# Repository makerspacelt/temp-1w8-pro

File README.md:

---

## ⚠️ __NEW USERS__
To set up your device with latest ESPHome config go to https://temp-1w8-pro.makerspace.lt/update

Latest ESPHome `*.yaml` file could be found in a dedicated software repository of this device: https://github.com/makerspacelt/temp-1w8-pro-sw

## About
This device is meant for temperature monitoring with up to 8 thermometers.

Basic target features:

* 8x 1-wire interfaces for DS18b20 using 2.5mm 4p audio jack connectors
* 2x user programmable buttons (can be used to wake up from deep sleep)
* 128x64 OLED display
* Powered via USB-C
* Compatibility with esphome and Home Assistant

Dev NOTE: before commit, run `./kibot.sh` to regenerate documentation, bom, gerbers and other assets.

* [schematics.pdf](gen/schematics.pdf)
* [pcb.pdf with dimensions](gen/pcb.pdf)
* [ibom.html](gen/single/ibom.html)

---

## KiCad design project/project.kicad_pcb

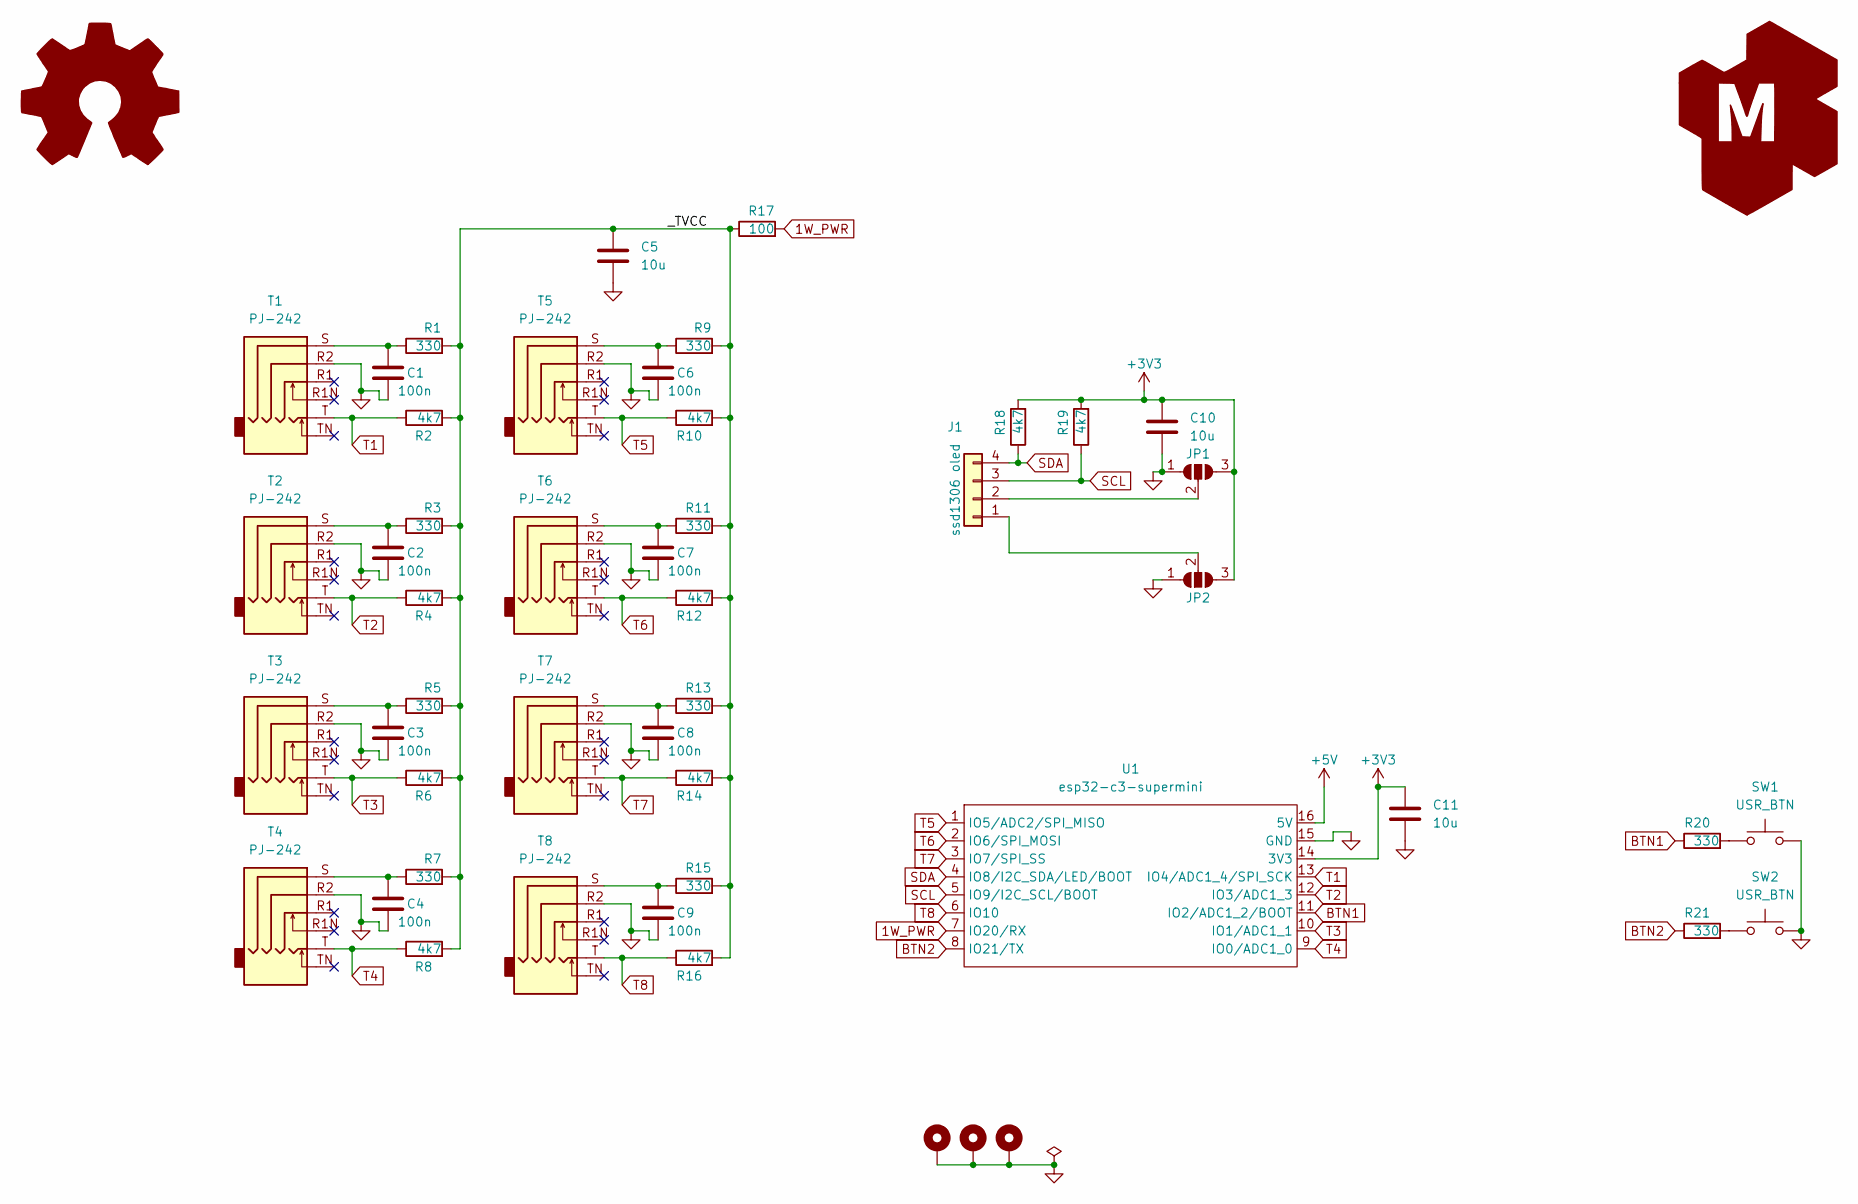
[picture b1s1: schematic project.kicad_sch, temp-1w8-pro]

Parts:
C1, C2, C3, C4, C6, C7, C8, C9: 100n; C_0805_2012Metric_Pad1.18x1.45mm_HandSolder; jlc-part-type B
C5, C10, C11: 10u; C_0805_2012Metric_Pad1.18x1.45mm_HandSolder; jlc-part-type B
G1: Logo_Open_Hardware_Large; OSHW-Symbol_6.7x6mm_SilkScreen
G2: LOGO_KMS; logo_kms_small_silkscreen
H1, H2, H3: MP; MountingHole_3.2mm_M3_DIN965_Pad
J1: ssd1306 oled; oled_i2c_1.3_128x64_ssd1306
JP1: PIN2; SolderJumper-3_P1.3mm_Open_RoundedPad1.0x1.5mm
JP2: PIN1; SolderJumper-3_P1.3mm_Open_RoundedPad1.0x1.5mm
R1, R3, R5, R7, R9, R11, R13, R15, R20, R21: 330; R_0805_2012Metric; jlc-part-type B
R2, R4, R6, R8, R10, R12, R14, R16, R18, R19: 4k7; R_0805_2012Metric; jlc-part-type B
R17: 100; R_0805_2012Metric; jlc-part-type B
SW1, SW2: USR_BTN; SW_SPST_TL3342; jlc-part-type B
T1, T2, T3, T4, T5, T6, T7, T8: PJ-242; lcsc# C5184834
U1: esp32-c3-supermini

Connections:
1W_PWR: R17.2, U1.7 (IO20/RX)
+3V3: C10.1, C11.1, JP1.3 (B), JP2.3 (B), R18.2, R19.2, U1.14 (3V3)
+5V: U1.16 (5V)
/_TVCC: C5.1, R1.2, R2.2, R3.2, R4.2, R5.2, R6.2, R7.2, R8.2, R9.2, R10.2, R11.2, R12.2, R13.2, R14.2, R15.2, R16.2, R17.1
BTN1: R20.1, U1.11 (IO2/ADC1_2/BOOT)
BTN2: R21.1, U1.8 (IO21/TX)
GND: C1.2, C2.2, C3.2, C4.2, C5.2, C6.2, C7.2, C8.2, C9.2, C10.2, C11.2, H1.1, H2.1, H3.1, JP1.1 (A), JP2.1 (A), SW1.2, SW2.2, T1.R2, T2.R2, T3.R2, T4.R2, T5.R2, T6.R2, T7.R2, T8.R2, U1.15 (GND)
unnamed: C1.1, R1.1, T1.S
unnamed: C2.1, R3.1, T2.S
unnamed: C3.1, R5.1, T3.S
unnamed: C4.1, R7.1, T4.S
unnamed: C6.1, R9.1, T5.S
unnamed: C7.1, R11.1, T6.S
unnamed: C8.1, R13.1, T7.S
unnamed: C9.1, R15.1, T8.S
unnamed: J1.1, JP2.2 (C)
unnamed: J1.2, JP1.2 (C)
unnamed: R20.2, SW1.1
unnamed: R21.2, SW2.1
SCL: J1.3, R19.1, U1.5 (IO9/I2C_SCL/BOOT)
SDA: J1.4, R18.1, U1.4 (IO8/I2C_SDA/LED/BOOT)
T1: R2.1, T1.T, U1.13 (IO4/ADC1_4/SPI_SCK)
T2: R4.1, T2.T, U1.12 (IO3/ADC1_3)
T3: R6.1, T3.T, U1.10 (IO1/ADC1_1)
T4: R8.1, T4.T, U1.9 (IO0/ADC1_0)
T5: R10.1, T5.T, U1.1 (IO5/ADC2/SPI_MISO)
T6: R12.1, T6.T, U1.2 (IO6/SPI_MOSI)
T7: R14.1, T7.T, U1.3 (IO7/SPI_SS)
T8: R16.1, T8.T, U1.6 (IO10)

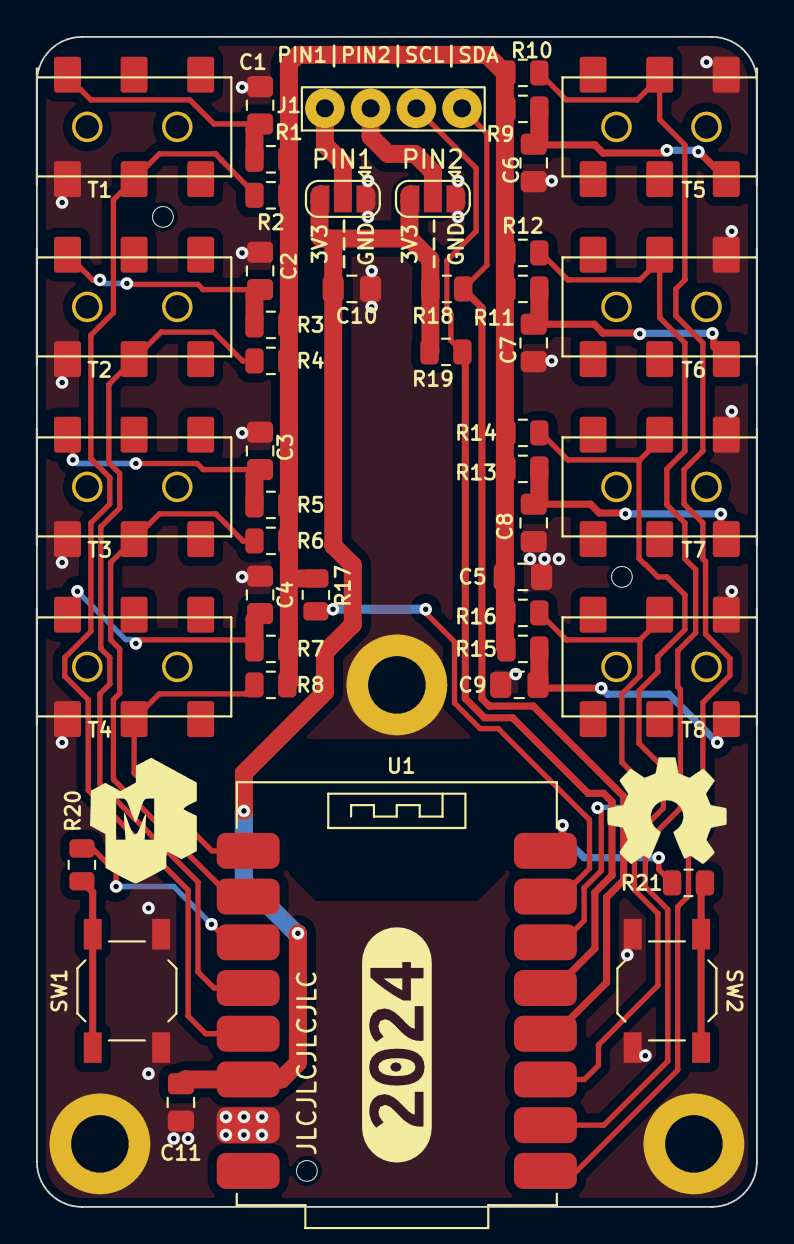
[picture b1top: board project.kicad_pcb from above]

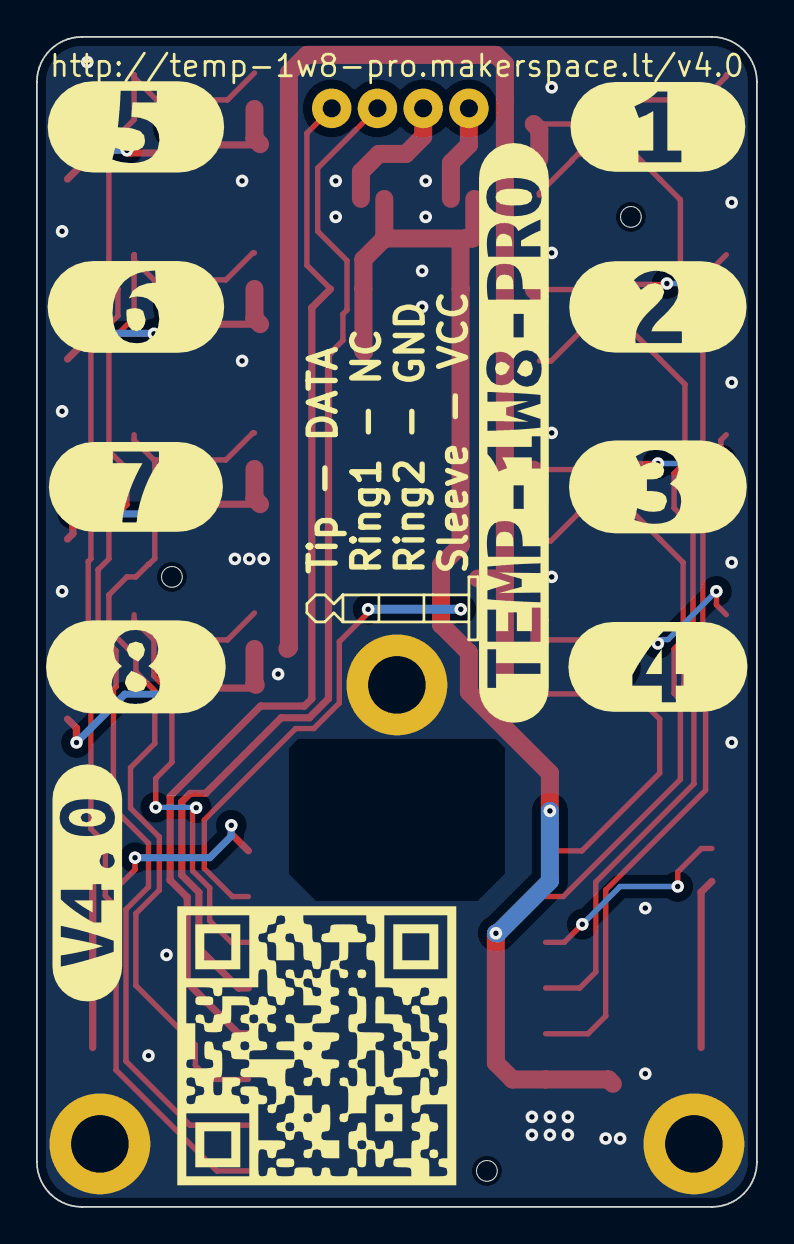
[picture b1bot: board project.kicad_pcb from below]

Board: 2 copper layers, 40.0 x 65.0 mm, 62 parts (10 on the bottom side), 28 nets.

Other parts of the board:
kibuzzard-66DA8205: G***; kibuzzard-66DA8205
kibuzzard-6769ACE8: G***; kibuzzard-6769ACE8
kibuzzard-6769ACFC: G***; kibuzzard-6769ACFC
kibuzzard-6769AD0A: G***; kibuzzard-6769AD0A
kibuzzard-6769AD2C: G***; kibuzzard-6769AD2C
kibuzzard-6769AD03: G***; kibuzzard-6769AD03
kibuzzard-6769AD10: G***; kibuzzard-6769AD10
kibuzzard-6769AD24: G***; kibuzzard-6769AD24
kibuzzard-6769B10C: G***; kibuzzard-6769B10C
kibuzzard-6771C807: G***; kibuzzard-6771C807
kibuzzard-669677F3: G***; kibuzzard-669677F3

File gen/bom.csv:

"Row","Description","Part","References","Value","Footprint","Quantity Per PCB","Status","Datasheet","lcsc#","jlc-part-type"
"1","Unpolarized capacitor","C","C1,C2,C3,C4,C5,C6,C7,C8,C12","100n","C_0805_2012Metric_Pad1.18x1.45mm_HandSolder","9"," ","~","C28233","B"
"2","Unpolarized capacitor","C","C9,C10,C11","10u","C_0805_2012Metric_Pad1.18x1.45mm_HandSolder","3"," ","~","C15850","B"
"3","RGB LED with integrated controller","WS2812B","D1","WS2812B","LED_WS2812B_PLCC4_5.0x5.0mm_P3.2mm","1"," ","https://cdn-shop.adafruit.com/datasheets/WS2812B.pdf","C2843785","E"
"4","Generic connector, single row, 01x04, script generated (kicad-library-utils/schlib/autogen/connector/)","Conn_01x04","J1","ssd1306 oled","oled_i2c_1.3_128x64_ssd1306","1"," ","~","","-"
"5","Resistor","R","R1,R3,R5,R7,R9,R11,R13,R15,R19,R20","330","R_0805_2012Metric","10"," ","~","C17630","B"
"6","Resistor","R","R2,R4,R6,R8,R10,R12,R14,R16,R17,R18","4k7","R_0805_2012Metric","10"," ","~","C17673","B"
"7","Push button switch, generic, two pins","SW_Push","SW1,SW2","USR_BTN","SW_SPST_PTS645","2"," ","https://wmsc.lcsc.com/wmsc/upload/file/pdf/v2/lcsc/210219150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","C2689405","E"
"8","Audio Jack, 4 Poles (Stereo / TRRS), Switched TR1 Poles (Normalling)","AudioJack4_SwitchTR1","T1,T2,T3,T4,T5,T6,T7,T8","PJ-242","PJ-242","8"," ","https://www.lcsc.com/datasheet/lcsc_datasheet_2210081801_han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","C5184834","E"
"9","","esp32-c3-supermini","U1","esp32-c3-supermini","esp32-c3-supermini","1"," ","","","-"

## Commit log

2024-07-16 adding first prototype
2024-07-17 adding missing models
2024-09-06 everything has changed
2024-09-12 adding link and qr code
2024-09-15 updating bom and pnp positions
2024-10-10 fixed bugs from v1.0
2024-12-01 adding hard reset for sensors, removing rgb led
2024-12-23 numbering inputs, changing buttons, and adding tooling holes
2024-12-29 replacing power fet with resistor
2025-04-17 ESPHome yaml config with font that displays all sensors on screen at once.
2025-05-02 Config updated to meet Made for ESPHome
2025-05-09 ID for i2c added.
2025-05-09 Comments fixed.
2025-06-10 adding OSHWA and shop links to README.md
2025-06-10 removing unused font
2025-07-11 adding link to software setup
2025-07-11 removing prototype notice
2025-07-13 removing config as software lives in new repo now
2025-07-18 Updated README with better instructions for initial user.
2025-07-18 Fixing README.
